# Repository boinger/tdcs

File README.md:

# tDCS — Open Source Transcranial Direct Current Stimulation

A complete, open-source hardware design for a transcranial direct
current stimulation (tDCS) device. The board uses an LM334Z current
regulator with a trimmer potentiometer to deliver an adjustable
0.5-2 mA constant current through sponge electrodes. Designed in
KiCad, fabrication-ready gerbers included for
[OSH Park](https://oshpark.com).

## Disclaimer

**This is an experimental device, not a medical device.** The authors
are not medical professionals. Use entirely at your own risk. Do not
treat this project as medical advice. Passing electric current through
your brain carries inherent risks. Read the published literature and
understand the schematics before attempting anything.

## Getting Started

**Prerequisites:** [KiCad](https://www.kicad.org/) 9.0 or later.

```bash
# macOS
brew install --cask kicad

# Linux (Ubuntu/Debian)
sudo apt install kicad
```

```bash
git clone https://github.com/boinger/tdcs
```

## Workflow

1. Open `tdcs.kicad_sch` in KiCad Schematic Editor — review/edit the circuit
2. Open `tdcs.kicad_pcb` in KiCad PCB Editor
3. **Tools → Update PCB from Schematic** to import components
4. Place components and route traces (reference `board.png` for original layout)
5. Run DRC (**Inspect → Design Rules Checker**)
6. Generate gerbers: `cd gerbers && ./generate-gerbers.sh`

### CLI Commands

```bash
# Export schematic as PDF
kicad-cli sch export pdf -o tdcs-schematic.pdf tdcs.kicad_sch

# Export BOM
kicad-cli sch export bom -o bom.csv tdcs.kicad_sch

# Export netlist
kicad-cli sch export netlist -o board.net tdcs.kicad_sch

# Run ERC (Electrical Rules Check)
kicad-cli sch erc tdcs.kicad_sch

# Generate gerbers (after PCB layout is complete)
cd gerbers && ./generate-gerbers.sh
```

## Getting the PCB Made

1. Upload `gerbers/tdcs.zip` to [OSH Park](https://oshpark.com) (or
   your preferred fab house).
2. Order parts from `bom.csv`.

## Accessories

Beyond the PCB and BOM components, you'll need:

- **Sponge electrodes** — the only electrode type with low enough
  impedance for reliable 2 mA delivery
- **Electrode cables** — speaker cable or lamp cord works fine
- **Pin connectors or banana plugs** — or solder cables directly to
  the board
- **12 V DC power supply** via barrel connector (or a 9 V battery
  if you only need up to ~1 mA)

## Safety

Liebetanz et al. (2009) established a brain-lesion threshold in rats
of **142.9 A/m²** sustained for >10 minutes
([DOI: 10.1016/j.clinph.2009.01.022](https://doi.org/10.1016/j.clinph.2009.01.022)).

This design uses 25 cm² sponge electrodes. Current densities:

| Condition | Current | Density | vs. Threshold |
|-----------|---------|---------|---------------|
| Normal operation | 2 mA | 0.8 A/m² | ~0.6% |
| Regulator failure (max) | 3 mA | 1.2 A/m² | ~0.8% |

Both cases are well below the damage threshold by two orders of
magnitude.

## Other Designs

The original upstream repo has branches for two additional designs:

- **v2** — MSP430-based programmable stimulator with USB power, data
  logging, and software-controlled current (via AD8400 digital pot)
- **v3** — Simplified USB-powered fixed-output (2 mA) stimulator

See [historical/](historical/) for archived blog posts describing
these designs.

## Repository Structure

| Path | Purpose |
|------|---------|
| `tdcs.kicad_sch` | Main schematic (KiCad Schematic Editor) |
| `tdcs.kicad_pcb` | Board layout (KiCad PCB Editor) |
| `tdcs.kicad_pro` | KiCad project file |
| `gerbers/` | Gerber output + `generate-gerbers.sh` |
| `gerbers/tdcs.zip` | Ready-to-upload zip for OSH Park |
| `datasheets/` | Component datasheets |
| `historical/` | Archived upstream blog posts, images, and gEDA design files |

## License

All files are licensed
[CC-BY 3.0](https://creativecommons.org/licenses/by/3.0/).
Full text in [LICENSE.txt](LICENSE.txt). Original design by
[Shawn Nock](https://github.com/nocko).

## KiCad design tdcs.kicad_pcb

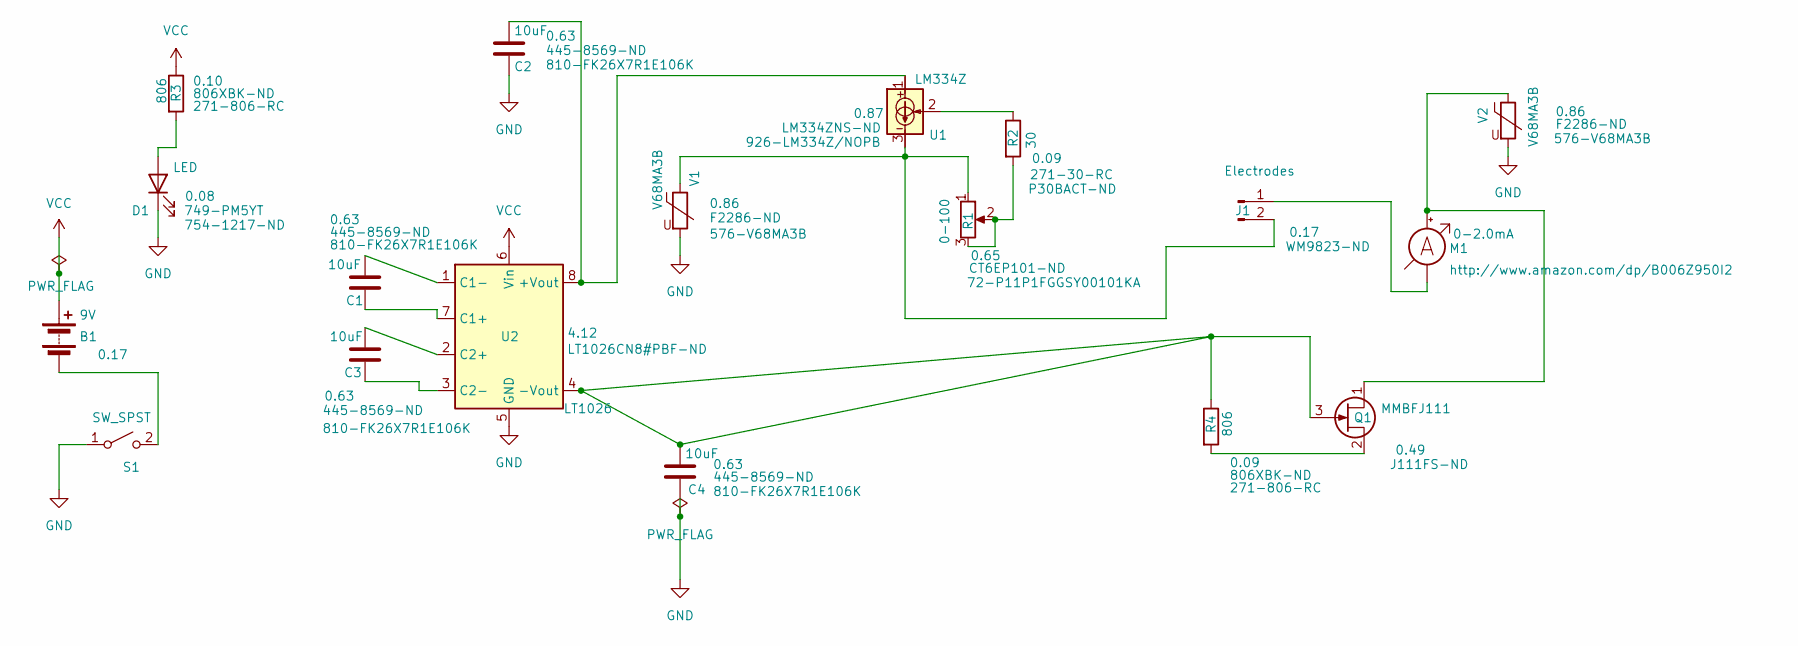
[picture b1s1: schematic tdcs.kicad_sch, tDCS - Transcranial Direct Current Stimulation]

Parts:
B1: 9V; PinHeader_1x02_P2.54mm_Vertical
C1, C2, C3, C4: 10uF; C_Disc_D5.0mm_W2.5mm_P5.00mm; DigiKey 445-8569-ND
D1: LED; LED_D3.0mm; DigiKey 754-1217-ND
J1: Electrodes; PinHeader_1x02_P2.54mm_Vertical; DigiKey WM9823-ND
M1: 0-2.0mA; PinHeader_1x02_P2.54mm_Vertical
Q1: MMBFJ111; TO-92_Inline; DigiKey J111FS-ND
R1: 0-100; PinHeader_1x03_P2.54mm_Vertical; DigiKey CT6EP101-ND
R2: 30; R_Axial_DIN0207_L6.3mm_D2.5mm_P7.62mm_Horizontal; DigiKey P30BACT-ND
R3, R4: 806; R_Axial_DIN0207_L6.3mm_D2.5mm_P7.62mm_Horizontal; DigiKey 806XBK-ND
S1: SW_SPST; PinHeader_1x02_P2.54mm_Vertical
U1: LM334Z; TO-92_Inline; DigiKey LM334ZNS-ND
U2: LT1026; DIP-8_W7.62mm; DigiKey LT1026CN8#PBF-ND
V1, V2: V68MA3B; R_Axial_DIN0207_L6.3mm_D2.5mm_P7.62mm_Horizontal; DigiKey F2286-ND

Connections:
GND: C2.2, C4.2, D1.1 (K), S1.1 (A), U2.5 (GND), V1.2, V2.2
unnamed: B1.2 (-), S1.2 (B)
unnamed: D1.2 (A), R3.2
unnamed: J1.1, M1.1 (-)
unnamed: J1.2, R1.1, U1.3, V1.1
unnamed: M1.2 (+), Q1.1 (D), V2.1
unnamed: C4.1, Q1.3 (G), R4.1, U2.4 (-Vout)
unnamed: Q1.2 (S), R4.2
unnamed: R1.2, R1.3, R2.2
unnamed: R2.1, U1.2
unnamed: C2.1, U1.1, U2.8 (+Vout)
unnamed: C1.2, U2.7 (C1+)
unnamed: C1.1, U2.1 (C1-)
unnamed: C3.1, U2.2 (C2+)
unnamed: C3.2, U2.3 (C2-)
VCC: B1.1 (+), R3.1, U2.6 (Vin)

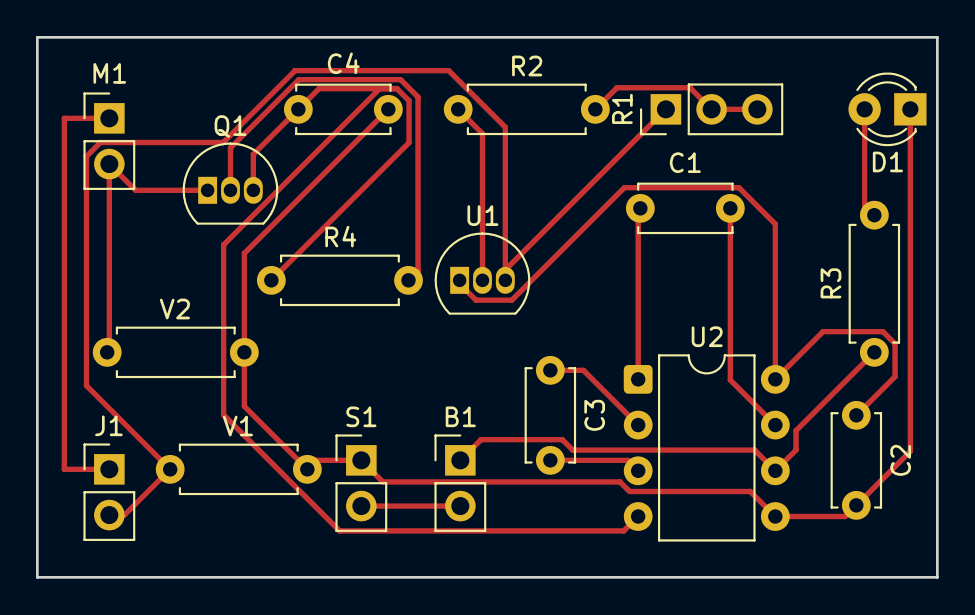
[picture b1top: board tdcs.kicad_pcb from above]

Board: 2 copper layers, 50.0 x 30.0 mm, 18 parts (0 on the bottom side), 16 nets.

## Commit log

2026-03-15 Rewrite README, fix paths, archive upstream materials
    - Full README rewrite: project description, safety analysis, disclaimer,
    accessories, workflow, repo structure
    - Add historical/ with archived blog posts and images from nocko.se
    (recovered via Wayback Machine)
    - Fix footprint path in project file (pcb_path → packages)
    - Fix generate-gerbers.sh portability (use $() instead of backticks)
2026-03-15 Update README to remove redundant author and license details
    Removed redundant original designer and licensing information from top section of README.
2026-03-16 Port tDCS project from gEDA to KiCad
    gEDA is unmaintained (no releases since 2013, removed from Homebrew).
    lepton-eda fork has broken macOS support. KiCad is the standard
    open-source EDA tool with active development and cross-platform support.
    Schematic port (tdcs.kicad_sch):
    - All 18 components with correct symbols, values, and footprints
    - All 16 nets verified against original board.net
2026-03-16 Add PWR_FLAG symbols to silence ERC power-not-driven errors
    KiCad ERC requires explicit PWR_FLAG markers on power nets to
    confirm they are intentionally driven. Added one on GND and one
    on VCC.
2026-03-16 Rearrange schematic layout for readability, fix LED orientation
    Components repositioned in KiCad GUI for clearer signal flow.
    Fixed D1 (LED) orientation — was reverse-biased after move.
    KiCad project file updated with DRC/ERC settings from GUI.
2026-03-17 Complete PCB layout with all components placed and routed
    2-layer board, all 18 THT components placed and traces routed.
    DRC passes clean.
2026-03-17 Regenerate gerber files from KiCad PCB layout
    7 gerber layers + drill file, zipped for OSH Park upload.
2026-03-17 Update supplier part numbers and pricing to current (March 2026)
    - R2: DigiKey P30BACT-ND (obsolete) → 30QBK-ND (YAGEO CFR-25JB-52-30R)
    - R2: Mouser 271-30-RC (discontinued) → 603-CFR-25JB-52-30R
    - D1: Mouser 749-PM5YT (wrong part) → 604-WP3A8GD (correct green 3mm LED)
    - U2: added Mouser 584-LT1026CN8#PBF
    - Q1: added Mouser 512-J111
    - R3/R4: Mouser updated to 603-MFR-25FBF52-806R
2026-03-17 Remove completed plan files
